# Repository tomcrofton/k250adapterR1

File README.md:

# k250adapterR1
This is the first version of the k250 adapter board.  A second version will follow that can be soldered directly to the raspberry pi pico.
A write-up of the k250 interface is in the files section over on groups.io (https://groups.io/g/KurzweilK250/topics)

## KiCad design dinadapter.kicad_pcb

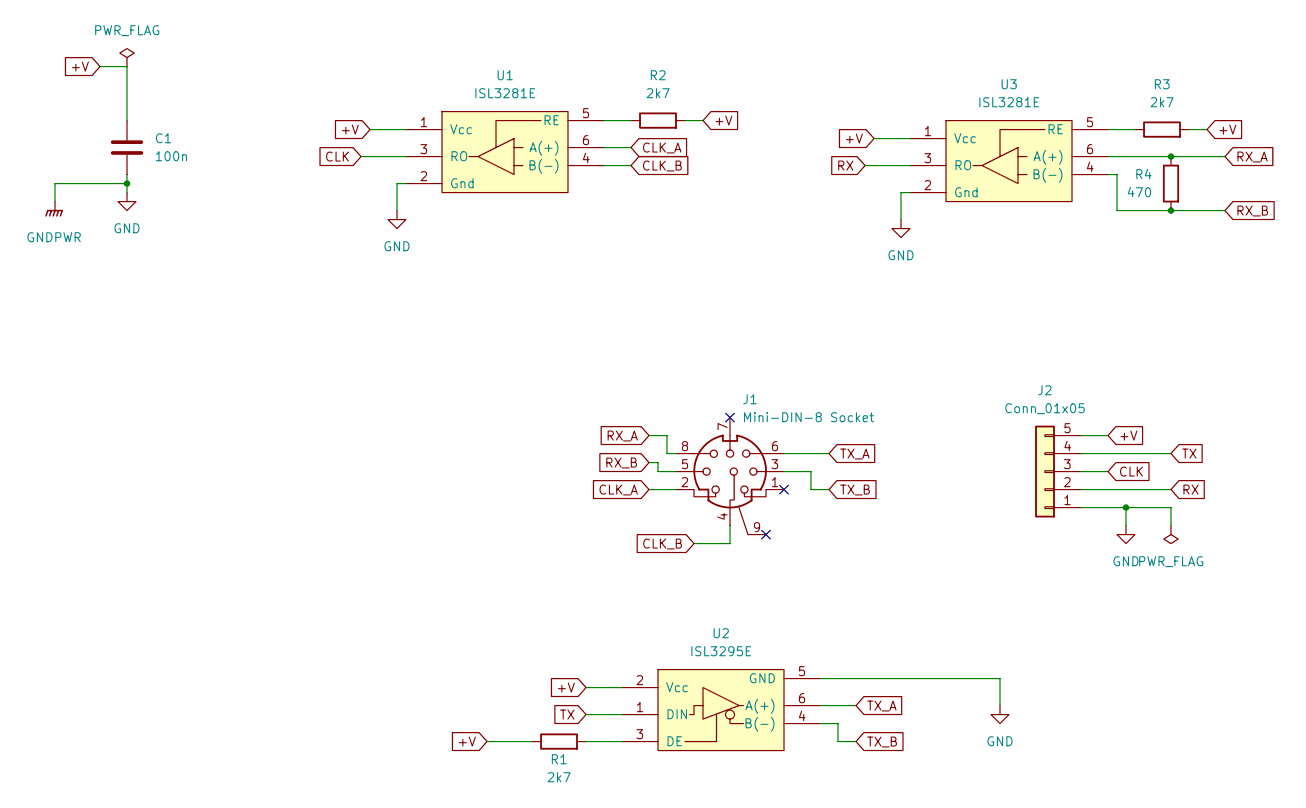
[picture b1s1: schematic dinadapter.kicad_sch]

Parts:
C1: 100n; C_0805_2012Metric_Pad1.18x1.45mm_HandSolder
J1: Mini-DIN-8 Socket; MiniDin8
J2: Conn_01x05; PinSocket_1x05_P2.54mm_Vertical
R1, R2, R3: 2k7; R_0805_2012Metric_Pad1.20x1.40mm_HandSolder
R4: 470; R_1206_3216Metric_Pad1.30x1.75mm_HandSolder
U1, U3: ISL3281E; SOT-23-6_Handsoldering
U2: ISL3295E; SOT-23-6_Handsoldering

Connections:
+V: C1.1, J2.5, R1.1, R2.2, R3.2, U1.1 (Vcc), U2.2 (Vcc), U3.1 (Vcc)
CLK: J2.3, U1.3 (RO)
CLK_A: J1.2, U1.6 (A(+))
CLK_B: J1.4, U1.4 (B(-))
GND: C1.2, J2.1, U1.2 (Gnd), U2.5 (GND), U3.2 (Gnd)
unnamed: R1.2, U2.3 (DE)
unnamed: R2.1, U1.5 (RE)
unnamed: R3.1, U3.5 (RE)
RX: J2.2, U3.3 (RO)
RX_A: J1.8, R4.1, U3.6 (A(+))
RX_B: J1.5, R4.2, U3.4 (B(-))
TX: J2.4, U2.1 (DIN)
TX_A: J1.6, U2.6 (A(+))
TX_B: J1.3, U2.4 (B(-))

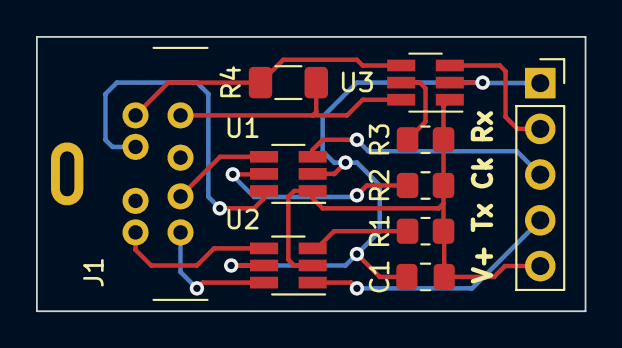
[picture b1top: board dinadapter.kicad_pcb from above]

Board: 2 copper layers, 30.5 x 15.2 mm, 10 parts (0 on the bottom side), 14 nets.
